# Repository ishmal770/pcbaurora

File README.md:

Simple PCB made during Aurora Hackathon
Pictures of work:

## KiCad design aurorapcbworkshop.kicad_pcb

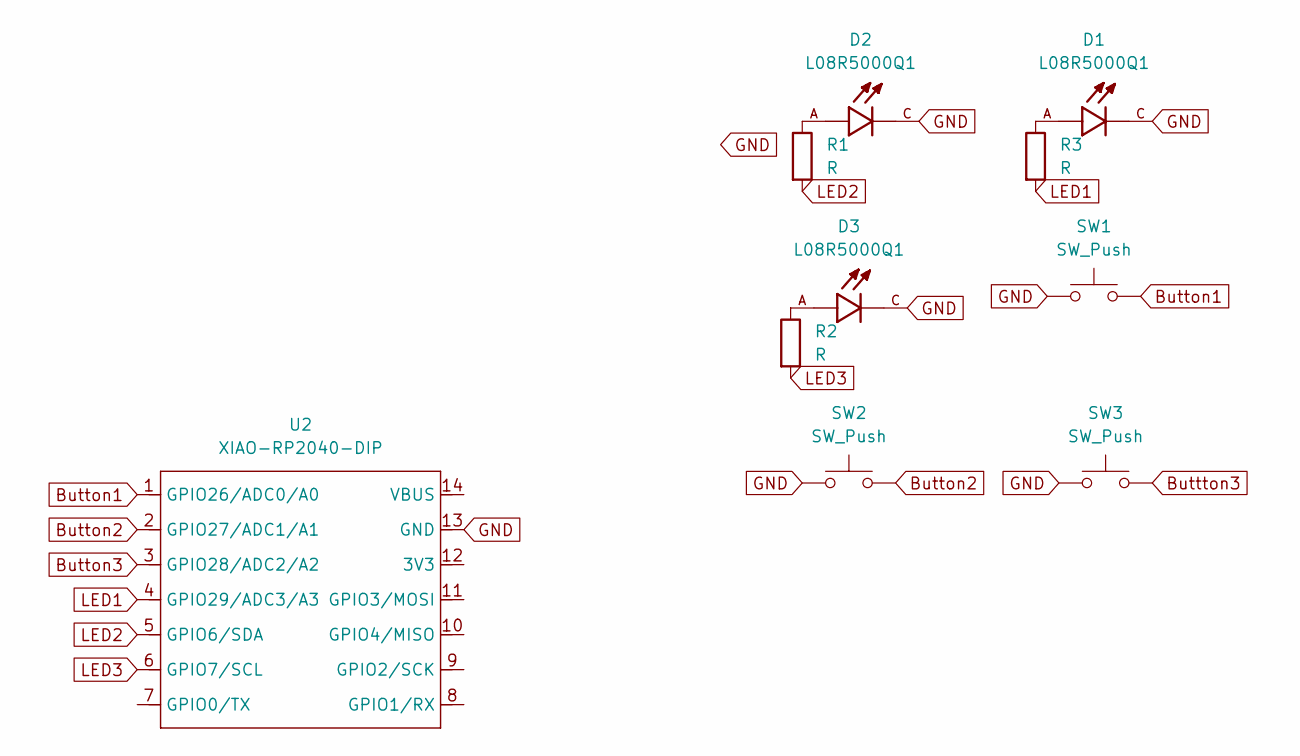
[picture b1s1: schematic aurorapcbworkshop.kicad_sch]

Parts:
D1, D2, D3: L08R5000Q1; LEDRD254W57D500H1070; PARTREV NA
R1, R2, R3: R; R_Axial_DIN0204_L3.6mm_D1.6mm_P5.08mm_Horizontal
SW1, SW2, SW3: SW_Push; SW_Cherry_MX_1.00u_PCB
U2: XIAO-RP2040-DIP; XIAO-RP2040-DIP (1)

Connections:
Button1: SW1.2, U2.1 (GPIO26/ADC0/A0)
Button2: SW2.2, U2.2 (GPIO27/ADC1/A1)
Button3: U2.3 (GPIO28/ADC2/A2)
Buttton3: SW3.2
GND: D1.C, D2.C, D3.C, SW1.1, SW2.1, SW3.1, U2.13 (GND)
LED1: R3.2, U2.4 (GPIO29/ADC3/A3)
LED2: R1.2, U2.5 (GPIO6/SDA)
LED3: R2.2, U2.6 (GPIO7/SCL)
unnamed: D1.A, R3.1
unnamed: D2.A, R1.1
unnamed: D3.A, R2.1

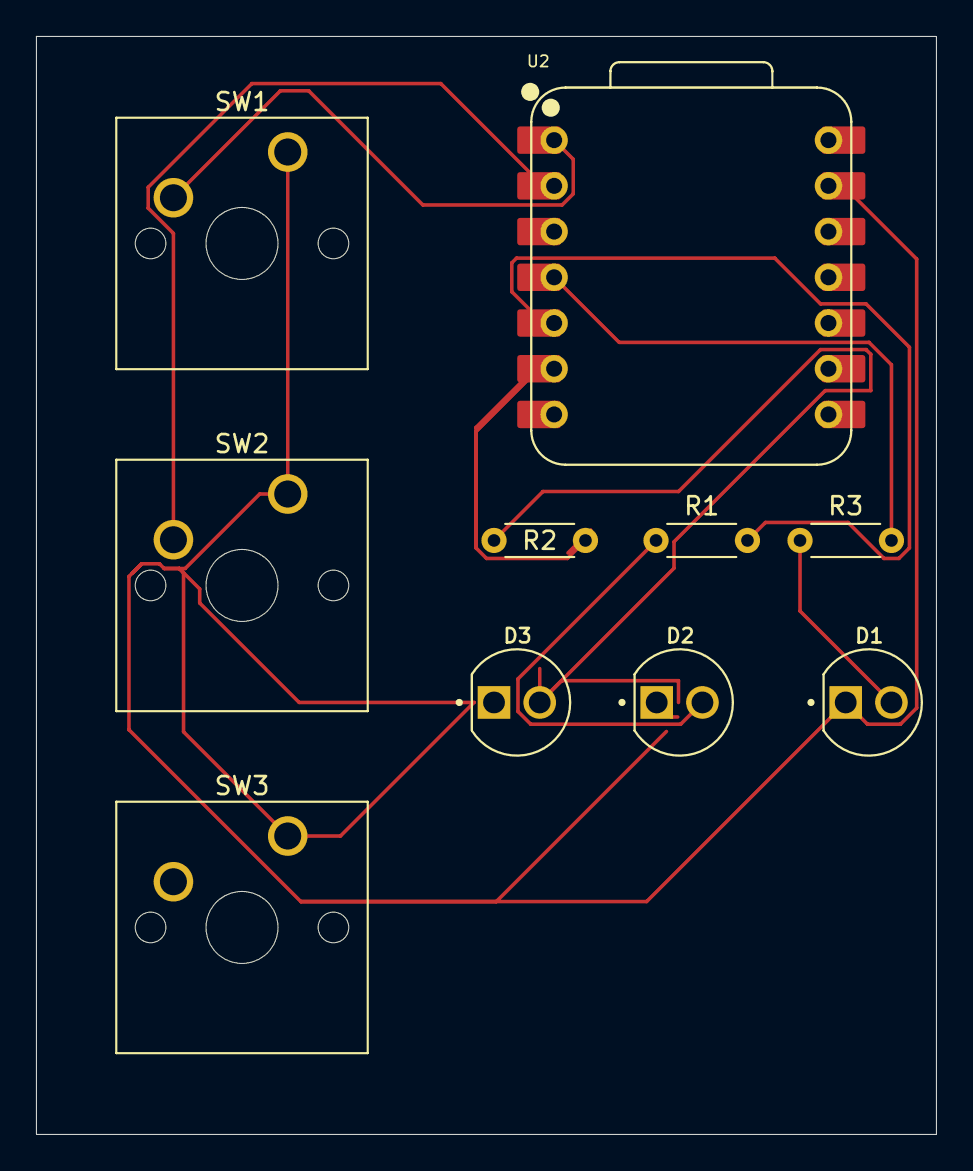
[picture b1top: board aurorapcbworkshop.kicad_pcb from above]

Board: 2 copper layers, 50.0 x 61.0 mm, 10 parts (0 on the bottom side), 9 nets.

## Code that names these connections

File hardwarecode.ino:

int pressed1 = 0;
int pressed2 = 0;
int pressed3 = 0;

int BUT1 = D0;
int BUT2 = D1;
int BUT3 = D2;

int LED1 = D3;
int LED2 = D4;
int LED3 = D5;

void setup() {
  pinMode(BUT1, INPUT);
  pinMode(BUT2, INPUT);
  pinMode(BUT3, INPUT);

  pinMode(LED1, OUTPUT);
  pinMode(LED2, OUTPUT);
  pinMode(LED3, OUTPUT);
}

void loop() {
  if (digitalRead(BUT1) == HIGH) {
    pressed1 = 1;
  }

  if (digitalRead(BUT2) == HIGH) {
    pressed2 = 1;
  }

  if (digitalRead(BUT3) == HIGH) {
    pressed3 = 1;
  }

  if (pressed1 == 1 && pressed2 == 1 && pressed3 == 1) {
    digitalWrite(LED1, HIGH);
    digitalWrite(LED2, HIGH);
    digitalWrite(LED3, HIGH);
  } else {
    digitalWrite(LED1, LOW);
    digitalWrite(LED2, LOW);
    digitalWrite(LED3, LOW);
  }
}

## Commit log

2025-07-20 code for pcb
2025-12-06 Add project description to README
2025-12-06 Add image to README for PCB proof
2025-12-06 Update image path for PCB proof in README
2025-12-06 Rename pcbproof1.png to CHECKIMAGE
2025-12-06 Rename PCBproof.png to CHECKIMAGE1
2025-12-06 Rename CHECKIMAGE to CHECKIMAGE.png
2025-12-06 Rename CHECKIMAGE1 to CHECKIMAGE1.png
2025-12-06 Add images of PCB work to README
    Added images of the PCB work to the README.
